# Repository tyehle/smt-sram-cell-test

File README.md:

# smt-sram-cell-test
A test of an S-RAM Cell

This was an initial attempt to make an S-RAM cell using surface mount parts. I now know that it does not work because the transistors aren't wired up properly. Oops!

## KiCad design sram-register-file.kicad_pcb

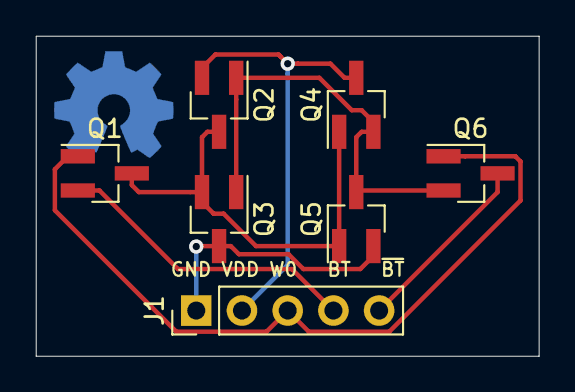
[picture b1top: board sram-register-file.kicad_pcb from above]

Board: 2 copper layers, 27.9 x 17.8 mm, 7 parts (0 on the bottom side), 7 nets.

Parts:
J1: Conn_01x05; PinHeader_1x05_P2.54mm_Vertical
Q1, Q3, Q5, Q6: NMOS; SOT-23_Handsoldering
Q2, Q4: PMOS; SOT-23_Handsoldering

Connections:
GND: J1.1, Q3.3, Q5.2
unnamed: J1.3, Q1.1, Q6.1
unnamed: J1.4, Q1.2
unnamed: J1.5, Q6.3
unnamed: Q1.3, Q2.3, Q3.2, Q4.1, Q5.1
unnamed: Q2.1, Q3.1, Q4.2, Q5.3, Q6.2
VDD: J1.2, Q2.2, Q4.3

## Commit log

2020-04-18 move cell to a folder
